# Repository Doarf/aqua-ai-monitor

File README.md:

# aqua-ai-monitor

<div align="center">

**Automated monitoring system for aquaculture basins**  
*IoT · Isolation Forest AI · MJPEG Video · Node.js · Flask · Chart.js*

</div>

---

## About the project

**aqua-ai-monitor** is a fully autonomous embedded platform for real-time aquaculture basin monitoring. It combines physicochemical sensor acquisition, live underwater video streaming, automatic CSV logging, and an on-the-fly trainable **Isolation Forest** anomaly detection model — all accessible from a web dashboard, with optional remote access via ngrok.

### The problem

Aquaculture basins require constant monitoring. A pH shift, rising turbidity or abnormal water conditions can cause significant losses within hours. Manual monitoring is expensive, discontinuous and reactive — the need is to be **proactive**.

### The solution

| Need | Solution |
|------|----------|
| Continuous acquisition | ESP32 reads 5 sensors every 2 s |
| Wi-Fi transmission | HTTP/JSON POST to Node.js server |
| Data history | Automatic CSV logging on PC |
| Anomaly detection | Isolation Forest (Python/Flask microservice) |
| Real-time visualization | Web dashboard with live charts (Chart.js) |
| Live video | ESP32-CAM + OV2640 → MJPEG stream |
| Remote access | ngrok HTTPS tunnel |

---

## Architecture

```
Physical sensors          OV2640 camera
      │                        │
      ▼ OneWire/ADC/I²C        ▼ MIPI CSI
  ESP32 Aqua              ESP32-CAM
      │                        │
      └──── Wi-Fi HTTP ─────────┘
                  │
                  ▼
        PC — Node.js (:3000) ◄──► Flask AI (:5001)
                  │                    │
                  │ ◄── /predict ───────┘
                  │
            data_aqua.csv  (auto-logged)
                  │
                  ▼
          Web Dashboard (:3000)
                  │
                  ▼ (optional)
          ngrok HTTPS tunnel
```

---

## Hardware components

| Component | Reference | Interface | Measured parameter |
|-----------|-----------|-----------|-------------------|
| Main microcontroller | ESP32-WROOM-32 | Wi-Fi, GPIO | Acquisition & transmission |
| Camera microcontroller | ESP32-CAM | Wi-Fi, MIPI CSI | Underwater video |
| Water temperature | DS18B20 | OneWire (GPIO 4) | Water temp (°C) |
| Air temp & humidity | DHT22 | Single-wire (GPIO 15) | Air temp (°C), humidity (%) |
| pH sensor | PH-4502C | ADC (GPIO 34) | pH (0–14) |
| Turbidity sensor | Keyestudio V1.0 | ADC (GPIO 35) | Turbidity (NTU) |
| Camera | OV2640 | MIPI CSI | JPEG VGA video |
| OLED display | SSD1306 128×64 | I²C (GPIO 21/22) | Local readout |

---

## Software stack

| Layer | Technology | Role |
|-------|-----------|------|
| Firmware | C++ / PlatformIO | Sensor reading, HTTP send |
| Server | Node.js / Express | Data relay, CSV logging, MJPEG proxy |
| AI service | Python / Flask | Isolation Forest training & inference |
| Dashboard | HTML/JS + Chart.js | Real-time charts, alerts, CSV upload |
| Remote access | ngrok | HTTPS tunnel |

---

## AI — Anomaly detection

The AI module uses an **Isolation Forest** model, trained on normal basin data collected by the system itself.

- **Unsupervised** — no labelled data required
- **Inputs** — pH and turbidity (NTU)
- **Double logic** — business rule thresholds + statistical IF score
- **Score** — normalized 0 (normal) → 1 (highly anomalous)
- **Trainable on the fly** — upload a CSV from the dashboard, click *Train*

```python
model = IsolationForest(n_estimators=200, contamination=0.05, random_state=42)
```

---

## Getting started

### Prerequisites

- Node.js ≥ 18
- Python ≥ 3.11
- PlatformIO
- ngrok (optional, for remote access)

### Launch the server & AI service

```bash
# Terminal 1 — Python AI microservice
cd esp32_cam_stream
pip install flask flask-cors scikit-learn pandas numpy joblib
python ai_service.py          # → http://localhost:5001

# Terminal 2 — Node.js server
cd esp32_cam_stream
npm install
node server.js                # → http://localhost:3000

# Terminal 3 — Remote access (optional)
ngrok http 3000
```

### Flash the ESP32 firmware

```bash
cd esp32_code/esp32_aqua
# Copy src/config_secret.h.example → src/config_secret.h
# Fill in your WIFI_SSID, WIFI_PASSWORD, SERVER_URL
pio run --target upload
pio device monitor --baud 115200
```

### Flash the ESP32-CAM

```bash
cd esp32_cam
# Copy src/config_secret.h.example → src/config_secret.h
# Fill in your WIFI_SSID and WIFI_PASSWORD
pio run --target upload
```

### Train the AI model

1. Let the system run for ~30 min under normal conditions
2. Open `http://localhost:3000`
3. Click **Download CSV** to get `data_aqua.csv`
4. Drag & drop the CSV into the AI panel → click **Train**
5. Model is active in under 1 second

---

## Repository structure

```
aqua-ai-monitor/
├── esp32_code/
│   └── esp32_aqua/              # Sensor firmware (PlatformIO)
│       └── src/
│           ├── main.cpp
│           ├── config.h
│           ├── config_secret.h.example
│           ├── ph_sensor.cpp/h
│           ├── turbidity_sensor.cpp/h
│           ├── ds18b20_sensor.cpp/h
│           ├── dht_sensor.cpp/h
│           ├── screen_oled.cpp/h
│           └── http_sender.cpp/h
├── esp32_cam/                   # Camera firmware (PlatformIO)
│   └── src/
│       ├── main.cpp
│       ├── camera.cpp/h
│       ├── streamer.cpp/h
│       ├── config.h
│       └── config_secret.h.example
├── esp32_cam_stream/            # Server + AI + Dashboard
│   ├── server.js                # Node.js/Express server
│   ├── ai_service.py            # Flask AI microservice
│   └── public/
│       └── index.html           # Web dashboard
├── SEBB_aqua/
│   └── carte_aqua/              # KiCad PCB project + Gerbers
├── docs/
│   └── banner.svg
├── rapport_aqua_ai_monitor.tex
└── rapport_aqua_ai_monitor.pdf
```

---

<div align="center">
  <sub>SPI Project · aqua-ai-monitor · IoT & AI for aquaculture</sub>
</div>

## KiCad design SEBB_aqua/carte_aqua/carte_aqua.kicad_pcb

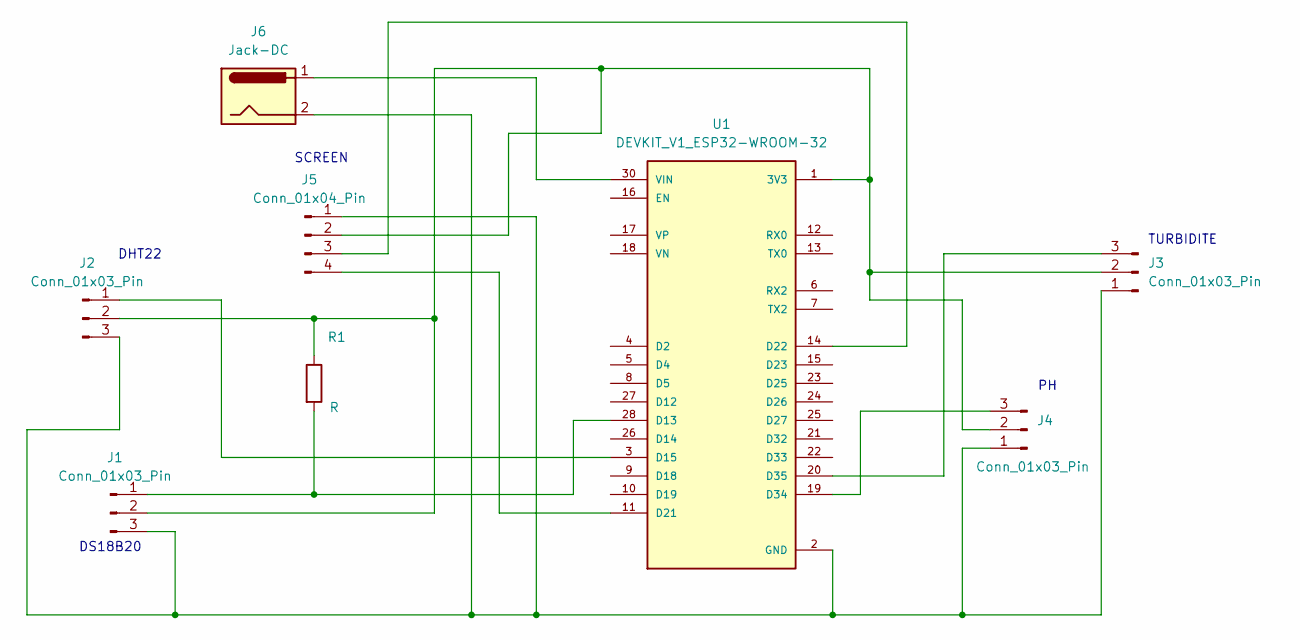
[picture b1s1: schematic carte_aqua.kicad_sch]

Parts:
J1, J2, J3, J4: Conn_01x03_Pin; JST_EH_B3B-EH-A_1x03_P2.50mm_Vertical
J5: Conn_01x04_Pin; JST_EH_B4B-EH-A_1x04_P2.50mm_Vertical
J6: Jack-DC; BarrelJack_CUI_PJ-063AH_Horizontal
R1: R; R_0603_1608Metric
U1: DEVKIT_V1_ESP32-WROOM-32; MODULE_DEVKIT_V1_ESP32-WROOM-32

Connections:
GND: J1.3, J2.3, J3.1, J4.1, J5.1, J6.2, U1.2 (GND), U1.29 (GND)
unnamed: J1.1, R1.2, U1.28 (D13)
unnamed: J1.2, J2.2, J3.2, J4.2, J5.2, R1.1, U1.1 (3V3)
unnamed: J2.1, U1.3 (D15)
unnamed: J3.3, U1.20 (D35)
unnamed: J4.3, U1.19 (D34)
unnamed: J5.3, U1.14 (D22)
unnamed: J5.4, U1.11 (D21)
unnamed: J6.1, U1.30 (VIN)

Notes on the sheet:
TURBIDITE
DHT22
SCREEN
DS18B20

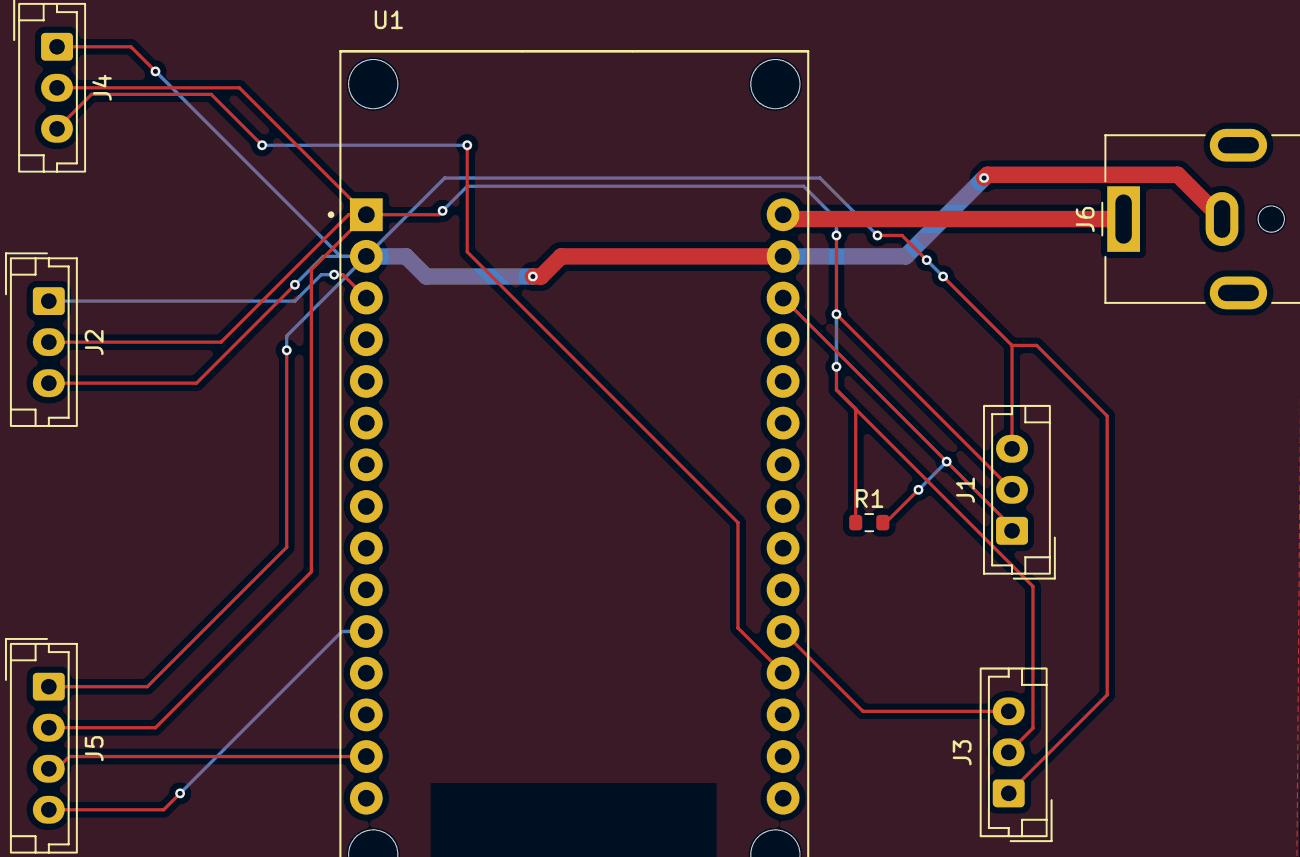
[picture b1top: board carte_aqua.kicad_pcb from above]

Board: 2 copper layers, 8 parts (0 on the bottom side), 9 nets.

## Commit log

2026-04-01 first commit esp32
2026-04-22 add turbidity sensor + calib
2026-04-26 board kicad
2026-04-29 add ds18b20
2026-05-19 feat: add AI anomaly detection (Isolation Forest), real-time charts, CSV logging, LaTeX report
2026-05-19 rapport udp
2026-05-19 maj main
2026-05-19 update main latex
2026-05-19 update main tex
2026-05-21 update latex
2026-05-21 update rd + latex
2026-05-21 tex maj
2026-06-30 security: isolate wifi credentials + video watchdog
    - Move SSID/password/SERVER_URL to config_secret.h (gitignored) for both ESP32 firmwares
    - Add config_secret.h.example for onboarding
    - Add video stream watchdog in dashboard (auto-retry on disconnect)
    - Remove duplicate data_aqua_ai.csv
2026-06-30 docs: add pixel art banner + update README
    - Add docs/banner.svg: pixel art fish with water background, bubbles, seaweed
    - Update README: banner at top, config_secret.h references in setup steps
2026-06-30 docs: simplify banner to pixel logo + English subtitle
2026-06-30 docs: replace banner with minimal pixel fish logo
2026-06-30 docs: update description
2026-06-30 docs: update README badges style

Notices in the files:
README.md:
License: MIT
